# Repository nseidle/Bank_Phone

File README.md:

Bank Phone
=========================

Bank Phone is an interactive exhibit at the [WOW kid's museum](http://www.wowchildrensmuseum.org/) in Lafayette, CO. When the user picks up the phone they hear a classic 'ring' tone, then one of 10 random tracks in English and Spanish. Dialing the dial causes that particular track (0 to 9) play.

The WOW Kid's museum wanted a rotary phone that automatically played a random track when a kid picked up the handset. If they dialed a number it would play the track associated with that number.

10 kid-friendly audio tracks (plus a 'ring ring' track) are loaded onto the microSD card. Power is provided from a 5V wall wart. The phone is screwed to a desk. 

This is [bakelite](https://en.wikipedia.org/wiki/Bakelite)! And yet 32,000 hands a month managed to destroy the handset. The replacement has been working well for over 2 years.

**Note:** The audio tracks must be converted to mono for this project. Use http://audio.online-convert.com/convert-to-wav to convert to mono.

This is the Arduino shield that connects to the various phone hook, dial, and return switch. There are ports for future expansion including an active ringer circuit and battery monitoring. Not needed for this exhibit.

Repository Contents
-------------------

* **firmware** - Contains the firmware that runs the phone
* **hardware** - Schematic and PCB layout for the shield that connects the dial and hook

License Information
-------------------
The hardware is released under [CERN Open Hardware License 1.2](http://www.ohwr.org/attachments/2388/cern_ohl_v_1_2.txt).
The code is beerware; if you see me (or any other SparkFun employee) at the local, and you've found our code helpful, please buy us a round!

Distributed as-is; no warranty is given.

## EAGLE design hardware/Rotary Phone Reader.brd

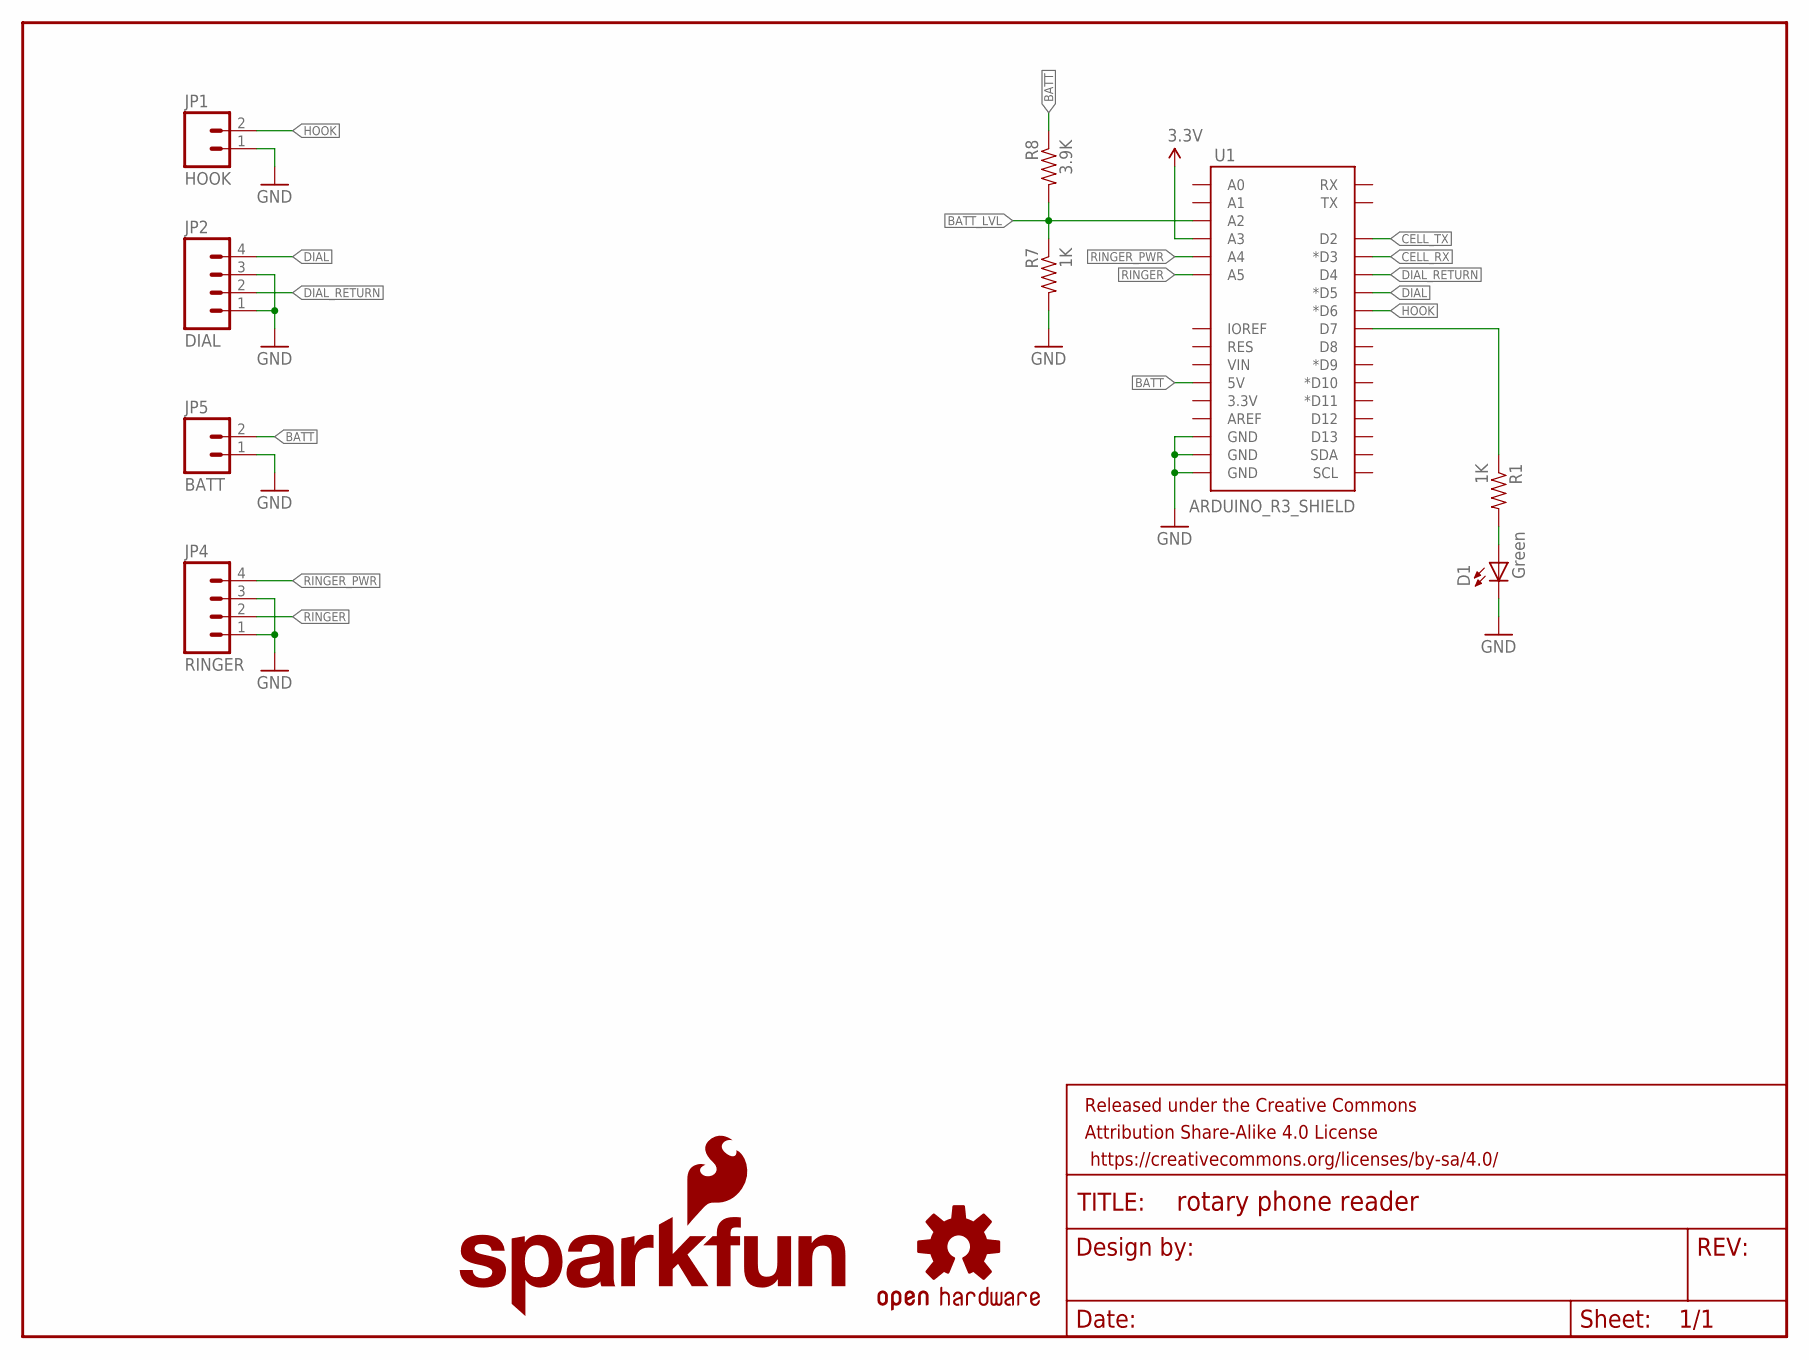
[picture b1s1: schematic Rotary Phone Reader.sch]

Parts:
D1: Green; LED5MM
FRAME1: FRAME-LETTER; CREATIVE_COMMONS
JP1: HOOK; JST-2-PTH
JP2: DIAL; JST-4-PTH
JP4: RINGER; JST-4-PTH
JP5: BATT; JST-2-PTH
LOGO1: SFE_LOGO_NAME_FLAME.1_INCH; SFE_LOGO_NAME_FLAME_.1
R1, R7: 1K; AXIAL-0.4
R8: 3.9K; AXIAL-0.4
U1: ARDUINO_R3_SHIELD; UNO_R3_SHIELD
U$7: OSHW-LOGOS; OSHW-LOGO-S

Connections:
3.3V: U1.A3
BATT: JP5.2, R8.P$1 (1), U1.5V
BATT_LVL: R7.P$1 (1), R8.P$2 (2), U1.A2
CELL_RX: U1.D3 (*D3)
CELL_TX: U1.D2
DIAL: JP2.4, U1.D5 (*D5)
DIAL_RETURN: JP2.2, U1.D4
GND: D1.K (C), JP1.1, JP2.1, JP2.3, JP4.1, JP4.3, JP5.1, R7.P$2 (2), U1.GND@0 (GND), U1.GND@1 (GND), U1.GND@2 (GND)
HOOK: JP1.2, U1.D6 (*D6)
unnamed: D1.A, R1.P$2 (2)
RINGER: JP4.2, U1.A5
RINGER_PWR: JP4.4, U1.A4
STAT1: R1.P$1 (1), U1.D7

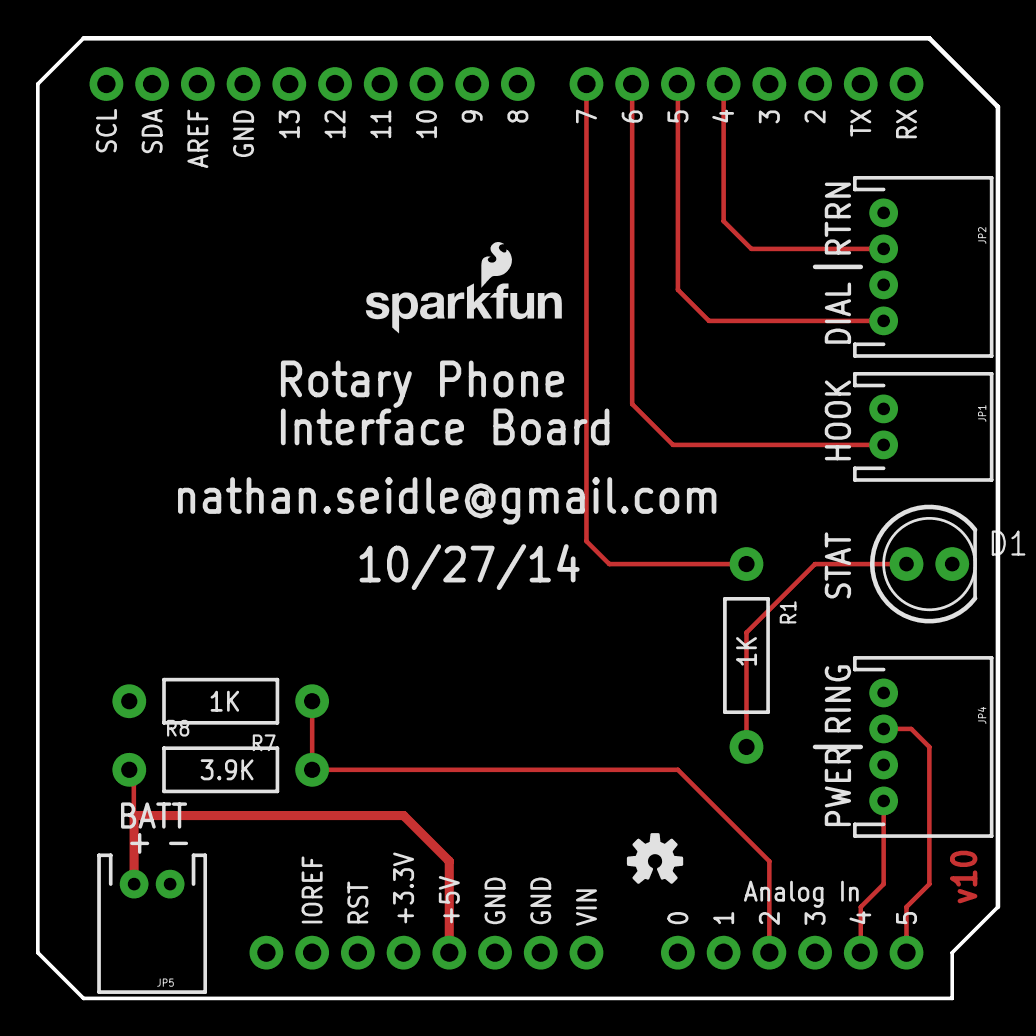
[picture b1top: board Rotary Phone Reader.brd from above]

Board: 2 copper layers, 53.3 x 53.3 mm, 12 parts (0 on the bottom side), 10 nets.

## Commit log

2014-10-28 :confetti_ball: Added .gitattributes & .gitignore files
2014-10-28 Adding board and basic firmware
2014-10-28 Tweaking readme
2014-10-28 Adding layout image to readme
2014-10-30 Finalizing firmware
    Uses a state machine to advance through the 5 different states: ON_HOOK,
    PLAY_RING, DIALING, PLAY_TRACK, DEAD_AIR.
2015-01-22 Now with latest audio files.
2015-02-02 Updated with Spanish language audio tracks
2015-02-24 Phone is freezing. Adding watchdog.
    And the children broke a backlight handset. It's incredible what small
    hands can do!
2016-03-09 Adding images and updating readme.
2016-03-09 Adding images to the readme.
2016-03-09 Adding images to readme.

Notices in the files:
parts and their libraries:
SparkFun-Aesthetics: Licensing: CC v3.0 Share-Alike You are welcome to use this library for commercial purposes.
SparkFun-Aesthetics: Released under the Creative Commons Attribution Share-Alike 4.0 License
SparkFun-Aesthetics: https://creativecommons.org/licenses/by-sa/4.0
